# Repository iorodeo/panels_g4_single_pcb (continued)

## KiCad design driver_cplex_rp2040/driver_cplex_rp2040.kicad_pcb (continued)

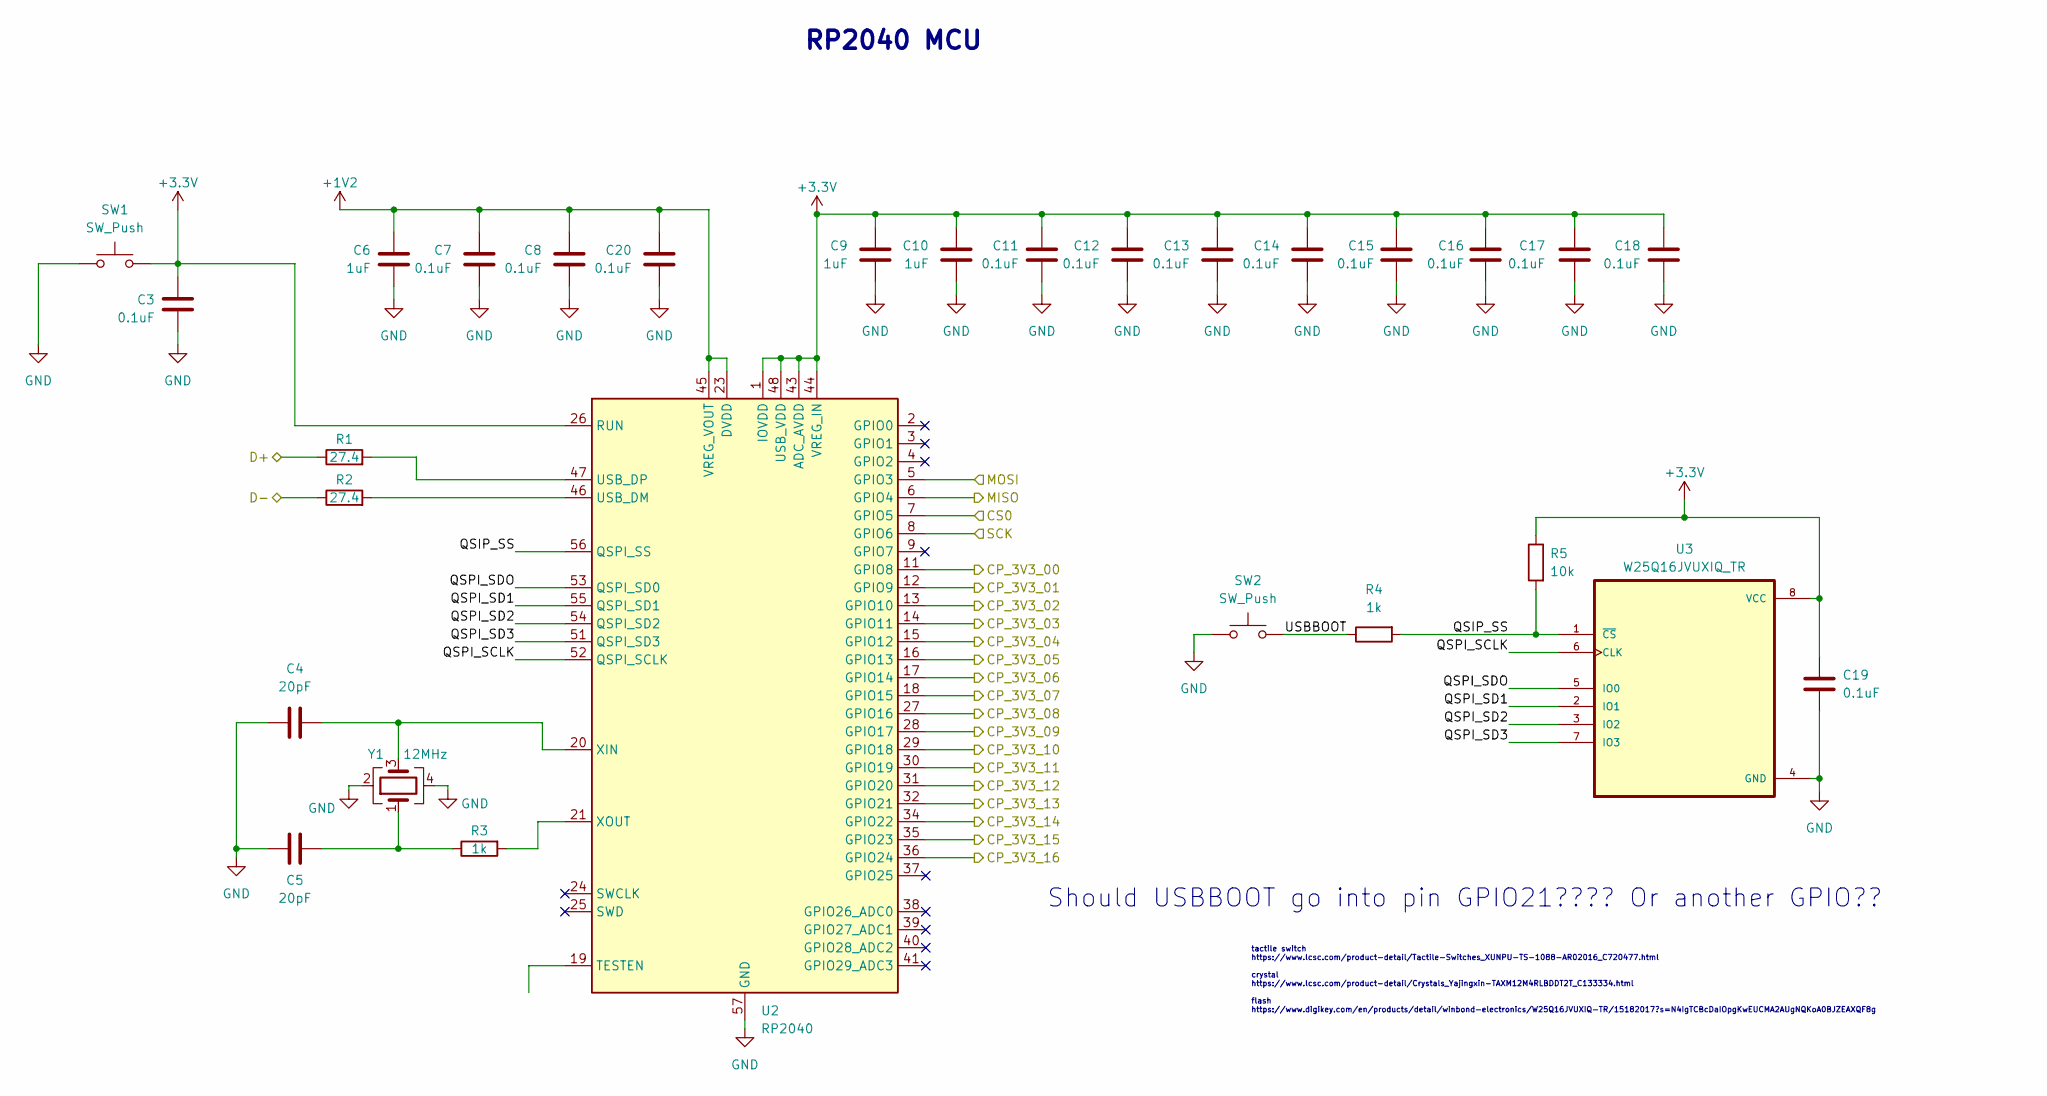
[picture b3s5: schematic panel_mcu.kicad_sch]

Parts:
C3, C7, C8, C11, C12, C13, C14, C15, C16, C17, C18, C19, C20: 0.1uF; C_0201_0603Metric
C4, C5: 20pF; C_0201_0603Metric
C6, C9, C10: 1uF; C_0201_0603Metric
R1, R2: 27.4; R_0201_0603Metric
R3, R4: 1k; R_0201_0603Metric
R5: 10k; R_0201_0603Metric
SW1, SW2: SW_Push; TS-1088-AR02016
U2: RP2040; QFN-56-1EP_7x7mm_P0.4mm_EP3.2x3.2mm
U3: W25Q16JVUXIQ_TR; flashmem_PSON50P300X200X60-9N
Y1: 12MHz; Crystal_SMD_3225-4Pin_3.2x2.5mm

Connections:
+1V2: C6.2, C7.2, C8.2, C20.2, U2.23 (DVDD), U2.45 (VREG_VOUT), U2.50 (DVDD)
+3.3V: C3.2, C9.2, C10.2, C11.2, C12.2, C13.2, C14.2, C15.2, C16.2, C17.2, C18.2, C19.2, R5.1, SW1.1, U2.1 (IOVDD), U2.10 (IOVDD), U2.22 (IOVDD), U2.26 (RUN), U2.33 (IOVDD), U2.42 (IOVDD), U2.43 (ADC_AVDD), U2.44 (VREG_IN), U2.48 (USB_VDD), U2.49 (IOVDD), U3.8 (VCC); also elsewhere on the board
/level_shifter/CP_3V3_00: U2.11 (GPIO8); also elsewhere on the board
/level_shifter/CP_3V3_01: U2.12 (GPIO9); also elsewhere on the board
/level_shifter/CP_3V3_02: U2.13 (GPIO10); also elsewhere on the board
/level_shifter/CP_3V3_03: U2.14 (GPIO11); also elsewhere on the board
/level_shifter/CP_3V3_04: U2.15 (GPIO12); also elsewhere on the board
/level_shifter/CP_3V3_05: U2.16 (GPIO13); also elsewhere on the board
/level_shifter/CP_3V3_06: U2.17 (GPIO14); also elsewhere on the board
/level_shifter/CP_3V3_07: U2.18 (GPIO15); also elsewhere on the board
/level_shifter/CP_3V3_08: U2.27 (GPIO16); also elsewhere on the board
/level_shifter/CP_3V3_09: U2.28 (GPIO17); also elsewhere on the board
/level_shifter/CP_3V3_10: U2.29 (GPIO18); also elsewhere on the board
/level_shifter/CP_3V3_11: U2.30 (GPIO19); also elsewhere on the board
/level_shifter/CP_3V3_12: U2.31 (GPIO20); also elsewhere on the board
/level_shifter/CP_3V3_13: U2.32 (GPIO21); also elsewhere on the board
/level_shifter/CP_3V3_14: U2.34 (GPIO22); also elsewhere on the board
/level_shifter/CP_3V3_15: U2.35 (GPIO23); also elsewhere on the board
/level_shifter/CP_3V3_16: U2.36 (GPIO24); also elsewhere on the board
/panel_header/MISO: U2.6 (GPIO4); also elsewhere on the board
/panel_header/MOSI: U2.5 (GPIO3); also elsewhere on the board
/panel_header/SCK: U2.8 (GPIO6); also elsewhere on the board
/panel_mcu/D+: R1.1; also elsewhere on the board
/panel_mcu/D-: R2.1; also elsewhere on the board
/panel_mcu/QSIP_SS: R4.2, R5.2, U2.56 (QSPI_SS), U3.1 (~CS)
/panel_mcu/QSPI_SCLK: U2.52 (QSPI_SCLK), U3.6 (CLK)
/panel_mcu/QSPI_SD1: U2.55 (QSPI_SD1), U3.2 (IO1)
/panel_mcu/QSPI_SD2: U2.54 (QSPI_SD2), U3.3 (IO2)
/panel_mcu/QSPI_SD3: U2.51 (QSPI_SD3), U3.7 (IO3)
/panel_mcu/QSPI_SDO: U2.53 (QSPI_SD0), U3.5 (IO0)
/panel_mcu/USBBOOT: R4.1, SW2.1
GND: C3.1, C4.2, C5.2, C6.1, C7.1, C8.1, C9.1, C10.1, C11.1, C12.1, C13.1, C14.1, C15.1, C16.1, C17.1, C18.1, C19.1, C20.1, SW1.2, SW2.2, U2.19 (TESTEN), U2.57 (GND), U3.4 (GND), Y1.2, Y1.4; also elsewhere on the board
unnamed: C5.1, R3.1, Y1.1
unnamed: R2.2, U2.46 (USB_DM)
unnamed: R1.2, U2.47 (USB_DP)
unnamed: C4.1, U2.20 (XIN), Y1.3
unnamed: R3.2, U2.21 (XOUT)

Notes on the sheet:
RP2040 MCU
tactile switch https://www.lcsc.com/product-detail/Tactile-Switches_XUNPU-TS-1088-AR02016_C720477.html crystal https://www.lcsc.com/product-detail/Crystals_Yajingxin-TAXM12M4RLBDDT2T_C133334.html flash https://www.digikey.com/en/products/detail/winbond-electronics/W25Q16JVUXIQ-TR/15182017?s=N4IgTCB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
Should USBBOOT go into pin GPIO21???? Or another GPIO??

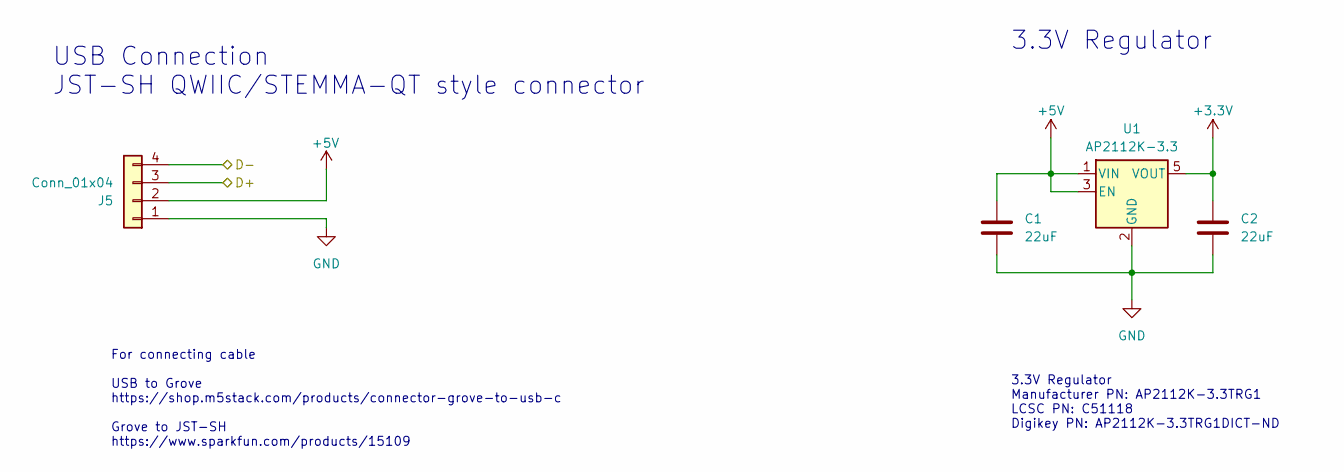
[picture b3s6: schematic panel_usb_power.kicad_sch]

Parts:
C1, C2: 22uF; C_0402_1005Metric
J5: Conn_01x04; JST_SH_SM04B-SRSS-TB_1x04-1MP_P1.00mm_Horizontal
U1: AP2112K-3.3; SOT-23-5

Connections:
+3.3V: C2.1, U1.5 (VOUT); also elsewhere on the board
+5V: C1.1, J5.2, U1.1 (VIN), U1.3 (EN); also elsewhere on the board
/panel_mcu/D+: J5.3; also elsewhere on the board
/panel_mcu/D-: J5.4; also elsewhere on the board
GND: C1.2, C2.2, J5.1, U1.2 (GND); also elsewhere on the board

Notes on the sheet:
USB Connection JST-SH QWIIC/STEMMA-QT style connector
For connecting cable USB to Grove https://shop.m5stack.com/products/connector-grove-to-usb-c Grove to JST-SH https://www.sparkfun.com/products/15109
3.3V Regulator
3.3V Regulator Manufacturer PN: AP2112K-3.3TRG1 LCSC PN: C51118 Digikey PN: AP2112K-3.3TRG1DICT-ND

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
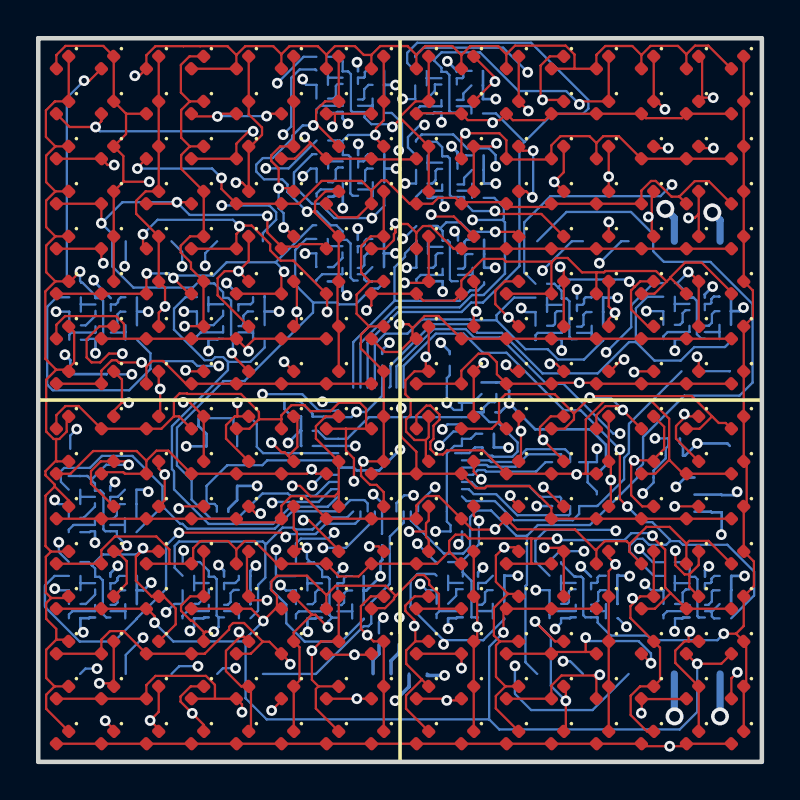
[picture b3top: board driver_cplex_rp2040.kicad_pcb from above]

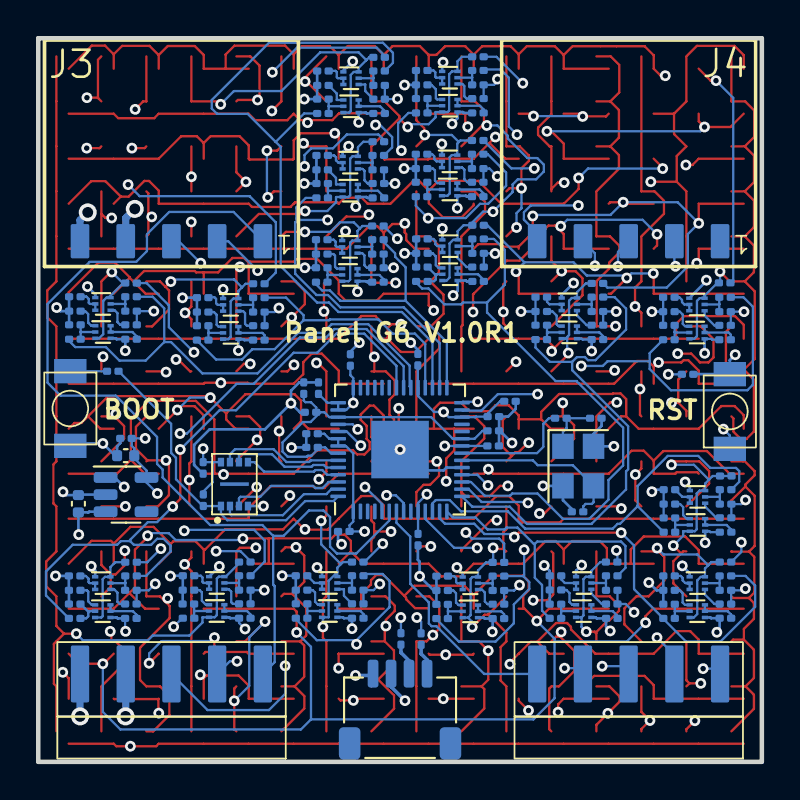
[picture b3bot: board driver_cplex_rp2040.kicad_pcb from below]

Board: 6 copper layers, 40.2 x 40.2 mm, 479 parts (223 on the bottom side), 178 nets.

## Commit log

2023-10-02 Project creation.
2023-10-02 Added readme.
2023-10-02 Fixed readme.
2024-03-10 Added charlie plexed version of single panel design.
2024-03-17 Minor mods to spice sims.
2024-03-18 Added Charlieplexed version of rp2040 single pcb design.
2024-03-18 Completed initial schematic of rp2040 design with charlieplexing.
2024-04-08 Worked on footprint assignment for rp2040 single panel cplex design.
2024-04-08 Worked on rp2040 cplex design layout.
2024-04-09 Worked on layout.
2024-04-11 minor mods to rp2040 cplex design.
2024-04-23 Worked on cplex driver layout.
2024-04-24 Worked on rp2040 cplex panel layout.
2024-04-29 Worked on rp2040 cplex layout.
2024-04-30 Worked on layout for rp2040 cplex'd panel.
2024-05-01 Worked on layout of rp2040 cplex design.
2024-05-02 Worked on layout for rp2040 cplex'd design.
2024-05-03 Added 3d model for RA 5POS conn header. Worked on layout.
2024-05-05 Worked on layout and routing for rp2040 cplexed panel.
2024-05-05 Worked on rp2040 cplex'd design.
    Tweaked layout and routing abit to assist routing.
2024-05-05 More work on routing.
2024-05-05 Added spectra session file for initial routing of rp2040 cplex'd design.
2024-05-06 Worked on routing and layut for rp2040 cplex'd design.
2024-05-06 Worked on routing and layout for rp2040 cplex'd design.
2024-05-07 Work on rp2040 cplex'd design routing and layout.
2024-05-08 Completed initial routing.
2024-05-08 Worked on silkscreen for rp2040 cplex design.
2024-05-20 Added spice models for chipiplexing.
2024-05-22 Worked on simulations.
2024-05-23 Worked on levelshifter simulation.
2024-05-23 Minor changes to spice sims.
2024-05-23 Added transistor spice sims.
2024-06-10 Worked on production files.
2024-07-08 Added finalized production files for v0.1r1.
2024-07-08 Fixed issue with solder mask on 1x5 conn rcpt.
2025-05-18 Worked on spice models.
2025-05-26 Added gate_driver simulation
2025-06-05 Added fit check for rp2350 design.
2025-06-06 More work on rp2350 fit check.
2025-06-08 Worked more on fit check / preliminary layout.
2025-06-09 Finished fit check layout for rp2350 design.
2025-06-09 Worked on rp2350 schematic.
2025-06-11 Finished first version of schematic for rp2350 G6 panel.
2025-07-13 Worked on new 18x18 led version of rp2350 design.
2025-07-14 Worked on modifications for rp2350 design.
2025-07-15 Worked on modifications for converting rp2350 design to 18x18 array.
2025-07-17 Worked on rp2350 driver layout.
2025-07-21 Modified for rp2354.
2025-07-21 Renamed LED array due to kicad compatibility issues.
2025-07-22 Worked on multi-color led layout.
2025-07-22 Worked on layout for 18x18 rp2354b panels.
2025-07-23 Worked on rp2354 panel layout.
2025-08-20 Worked on 20x20 design.
2025-08-25 More work on rp2350 20x20 panel.
2025-08-25 Work on layout for rp2350 20x20 array panels.
2025-08-25 Worked on layout and routing for rp2350 20x20 array panel.
2025-08-26 Worked on rp2350 20x20 panel layout and routing.
2025-08-27 Worked on rp2350 20x20 panel routing.
2025-08-27 Finished initial manual routing for rp2350 20x20 panel.
2025-08-28 Worked on layout and routing for rp2350 20x20 panels.
2025-08-28 Completed first route of rp2350 20x20 panel design.
2025-09-08 Working on 2nd layout & route for rp2350 20x20 panel design.
2025-09-09 Completed 2nd layout/routing of rp2350 20x20 panel.
    I've eliminated all design rule checker errors. Still need to double
    check to make sure everything is OK with pcb manufactures guidelines.
2025-09-10 Worked on setup for fabrication.
2025-09-12 Worked on fab files.
2025-09-16 Worked on routing and fabrication setup.
2025-09-17 Worked on routing, layout and fab setup for rp2354b 20x20 panel.
2025-09-22 Work on finalizing layout/routing and fab files.
2025-09-23 Renamed to panel_rp2354_20x20. Creaetd inition production files.
2025-09-24 Worked on rp2354 fabrication files.
2025-09-29 Fixed part rotation issues. Remove J2 J3 LCSC part as it was incorrect.
2025-09-29 Added some notes.
2025-09-30 Fixed net label issue ... changes CS3 to CS4.
